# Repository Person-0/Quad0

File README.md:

# **Quad0**

*quadcopter with a custom flight controller, firmware that supports both brushed and brushless motors*

## **The Idea**
This is a custom flight controller with minimal stuff required to fly a quadcopter on-board, supporting both brushless and brushed motors.

Onboard components include:

- `RP2350A` Microcontroller Unit
- **IMU**:
    - `ICM-42688-P` Accelerometer & Gyroscope
    - `DPS368XTSA1` Barometer
    - `BMM150` Magnetometer

- MOSFET motor drivers (`DMN2024UFDF-7`) for brushed motors
- Pads to connect brushed / brushless motors
- Support for `ESP01 WiFi module` for brushed mode OR any radio receiver that supports SBUS or similar protocols for brushless mode

The board will be designed in a way such that it can fly with standard *8520 coreless motors* and a tiny lipo battery for brushed mode.

As for the brushless mode, I will be targeting `2204` size brushless motors with a `5inch` prop size, ~5inch frame configuration.

> For building, skip to [Build instructions](#build-instructions) section.

## **PCB**

The PCB 3D preview looks like this:

## **Schematics**

> *[Right Click >> Open in new tab] on the image to view properly.*

> Note that the PCB and schematic files can be opened using KiCAD. They are located in the `/PCB/Quad0` directory inside this repository.

Steps for viewing the PCB schematics and layout:
- Open KiCAD
- Click **File** (top left) >> **Open Project**
- Navigate to the the repository's saved destination,
- Open **/PCB/Quad0** directory
- Select the file `Quad0.kicad_pro`

## Brushed / Brushless Switch

- **Yellow**: Brushed motor connectors
- **Red**: Brushed / Brusheless Mode selection connector

**For Brushed:** Short both pads together using solder or by soldering 2.54mm headers and adding jumper.

**For Brushless:** Un-short both pads if shorted, connect ESC signal pin to the pad marked with the thick white circle.

Each Mode selection connector is placed closest to the motor output it controls.

## **CAD Frame**
> View [/CAD](./CAD/) directory for `.f3d` and `.step` files.

The frame for brushed version of the quadcopter was designed in Fusion360 and looks like this:

**The frame is divided into 3 separate parts:**

- **Main Frame:**

- **Duct Body:**

- **Cover:**

All the parts are made to friction-fit together using cylindrical extrusions and holes, the reason being to minimize the weight of the frame as using screws would add a LOT of weight. The friction fits would allow for either the cover or duct body to be omitted incase they are adding too much weight.

## **Firmware**

*Please checkout the [/Firmware](./Firmware/) directory to view the firmware source, current state and compiling / flashing instructions.*

> Note that the hardware is also [fully supported](https://betaflight.com/blog/2025/10/10/RP2350%20Lands%20in%20Betaflight) by [Betaflight](https://betaflight.com/). Instructions on how to setup betaflight will be provided after I physically test it myself to know what works.

## **Ordering Parts, PCBA**
1. **PCBA**

Files required (gerber, bom, cpl) for ordering PCB Assembly from JLCPCB are available in [PCB/Ordering/](./PCB/Ordering/) directory.

The grand total for this comes out to be at `$108.95`, including `$9.86` for shipping. This cost can be brought down using coupon codes and also using JLCPCB'S desktop app: JLCONE.

This is after minimizing extended components usage and using basic PCBA (cheapest option). The PCB quantity and PCBA quantity is the MOQ (minimum order quantity): 5, 2 respectively.

**Cart Screenshot:**

2. **Other components**

Components required other than the ones that the PCBA covers are the following (for brushed mode):
- 4x Coreless Motors
- 4x 65mm propellers (2CW + 2CCW)
- 1x 1N5819 Diode (6V version recommended)
- 1x 3.7v tiny LiPo battery (+ a charger for it if you do not have one). Recommended capacity ~350-500mAh, try to minimize weight
- 1x ESP-01 WiFi Module
- 2.54mm header pins as required (only if you need them, otherwise you can directly solder the wires to the pads)

### **BOM** (Region: India)
---
| S.No. | Item Name | Item Description | URL | Qty | Unit Price ($) | Effective Price ($) |
|---:|---|---|---|---:|---:|---:|
| 1 | JLCPCB Order | 5x PCB + 2x PCBA | - | 1 | 99.09 | 99.09 |
| 2 | JLCPCB Shipping | Shipping costs | - | 1 | 9.86 | 9.86 |
| 3 | 8520 Coreless Brushed Motor | 8520 Coreless motor | https://makerbazar.in/products/magnetic-micro-coreless-motor-for-drones-quadcopters-rc?variant=44950426812656 | 4 | 0.72 | 2.88 |
| 4 | 65mm 2 Blade Toothpick Propeller 1mm Shaft Pitch 1.3" Clear Red (4 Pair CW+CCW) | 65mm Propeller | https://evelta.com/gemfan-65mm-2-blade-toothpick-propeller-1mm-red/?sku=479-PMPC65S-R1&utm_matchtype=&utm_term=&adgroupid=&gc_id=21398421111&h_ad_id= | 1 | 2.20 | 2.20 |
| 5 | 1N5819 40V 1A Schottky Diode - Pack of 10 | Diode for reverse polarity protection | https://makerbazar.in/products/1n5819-schottky-diode-1a-40v-do-41?variant=48251131527408 | 1 | 0.20 | 0.20 |
| 6 | 3.7V 500mAH LiPo battery | 500 mAh LiPo battery | https://makerbazar.in/products/kp-drone-lipo-batteries-3-7v-rechargeable-battery-for-mini-rc-aircraft-quadcopters?variant=48251096662256 | 1 | 2.81 | 2.81 |
| 7 | ESP-01 ESP8266 Serial WIFI Transceiver Module | ESP01 WiFi module | https://makerbazar.in/products/esp8266-wifi-module-for-arduino?variant=31789289898080 | 1 | 1.41 | 1.41 |
| | | | | | **Total:** | **127.50** |

This does not include shipping costs for components other than PCB+PCBA, since that will differ from place-to-place.

## **Build Instructions**

The project build is divided into 4 parts:
1. PCB, Components ordering
2. Soldering external components onto the PCB
3. 3D printing the frame
4. Compiling, Flashing the firmware.

### 1.) PCB, Components Ordering
Please refer the [Ordering Parts, PCBA](#ordering-parts-pcba) section for this step.

### 2.) Soldering external components onto the PCB
Various components are required to be externally hand soldered onto the PCB. Focusing on the brushed mode, these are the components:
1. **Brushed Motors**: These need to be soldered to the motor pads at the corner ends of the PCB. Make sure that the Mode selection connector pads that are present near the motor connectors are shorted for brushed mode. This might require re-soldering to change motor polarity so keep that in mind.
2. **1N5819 Diode**: This needs to be soldered on the 2.54mm header pad with silkscreen marked as "1N5819". The cathode should be connected to the pad with the silkscreen square connected to the silkscreen text (This is the +BATT_Brushed pad).
3. **Battery Connector**: Marked as "Power IN" on the silkscreen with + and - symbols, either use JST style male-female connectors (preferred) or simple jumper wires. Solder the female connector to the PCB and the male one to the battery terminals. Ensure you can charge the battery easily and handle the LiPo batteries properly as they are extremely dangerous. Battery can be fixed using rubber bands or double-sided tape onto the backside of the frame. Make sure to center it as accurately as close to the Quad's centre-of-gravity, so as to ensure stable flight
4. **ESP-01**: Solder the ESP-01 module to the top footprint defined for it. You can refer the 3D frame render for orientation as it shows the correct way it needs to be placed. Your module most likely will already have headers soldered onto it, you just need to solder it onto the PCB.
5. **GPIO Pins (optional)**: At the bottom of the PCB, if needed, solder female header pins or just solder the extra components directly.

### 3.) 3D printing the frame + assembling
The following three `.step` files need to be 3d printed separately using a lightweight but sturdy material of your choice: (I will be testing it out myself, starting with PLA)
- [MainBody.step](./CAD/exports/MainBody.step)
- [DuctBody.step](./CAD/exports/DuctBody.step)
- [Cover.step](./CAD/exports/Cover.step)

After that, It is recommended to test the quad with just the MainBody and then progressively add the DuctBody, Cover. This helps to ensure that the drone actually flies and is not held down by the weight of the frame.

The PCB sits on the cylindrical extrusions defined for it (as shown in the preview images). You can add tiny foam/similar rings between the PCB and the plastic body to dampen motor vibrations. Use adhesive tape (or whatever you prefer) to firmly hold the PCB in place with the main body, while also making sure you do not add extra unnecessary weight.

### 4.) Compiling, Flashing the firmware
Please refer the [/Firmware](./Firmware/) directory for this step.

That's it!

## 😼💖

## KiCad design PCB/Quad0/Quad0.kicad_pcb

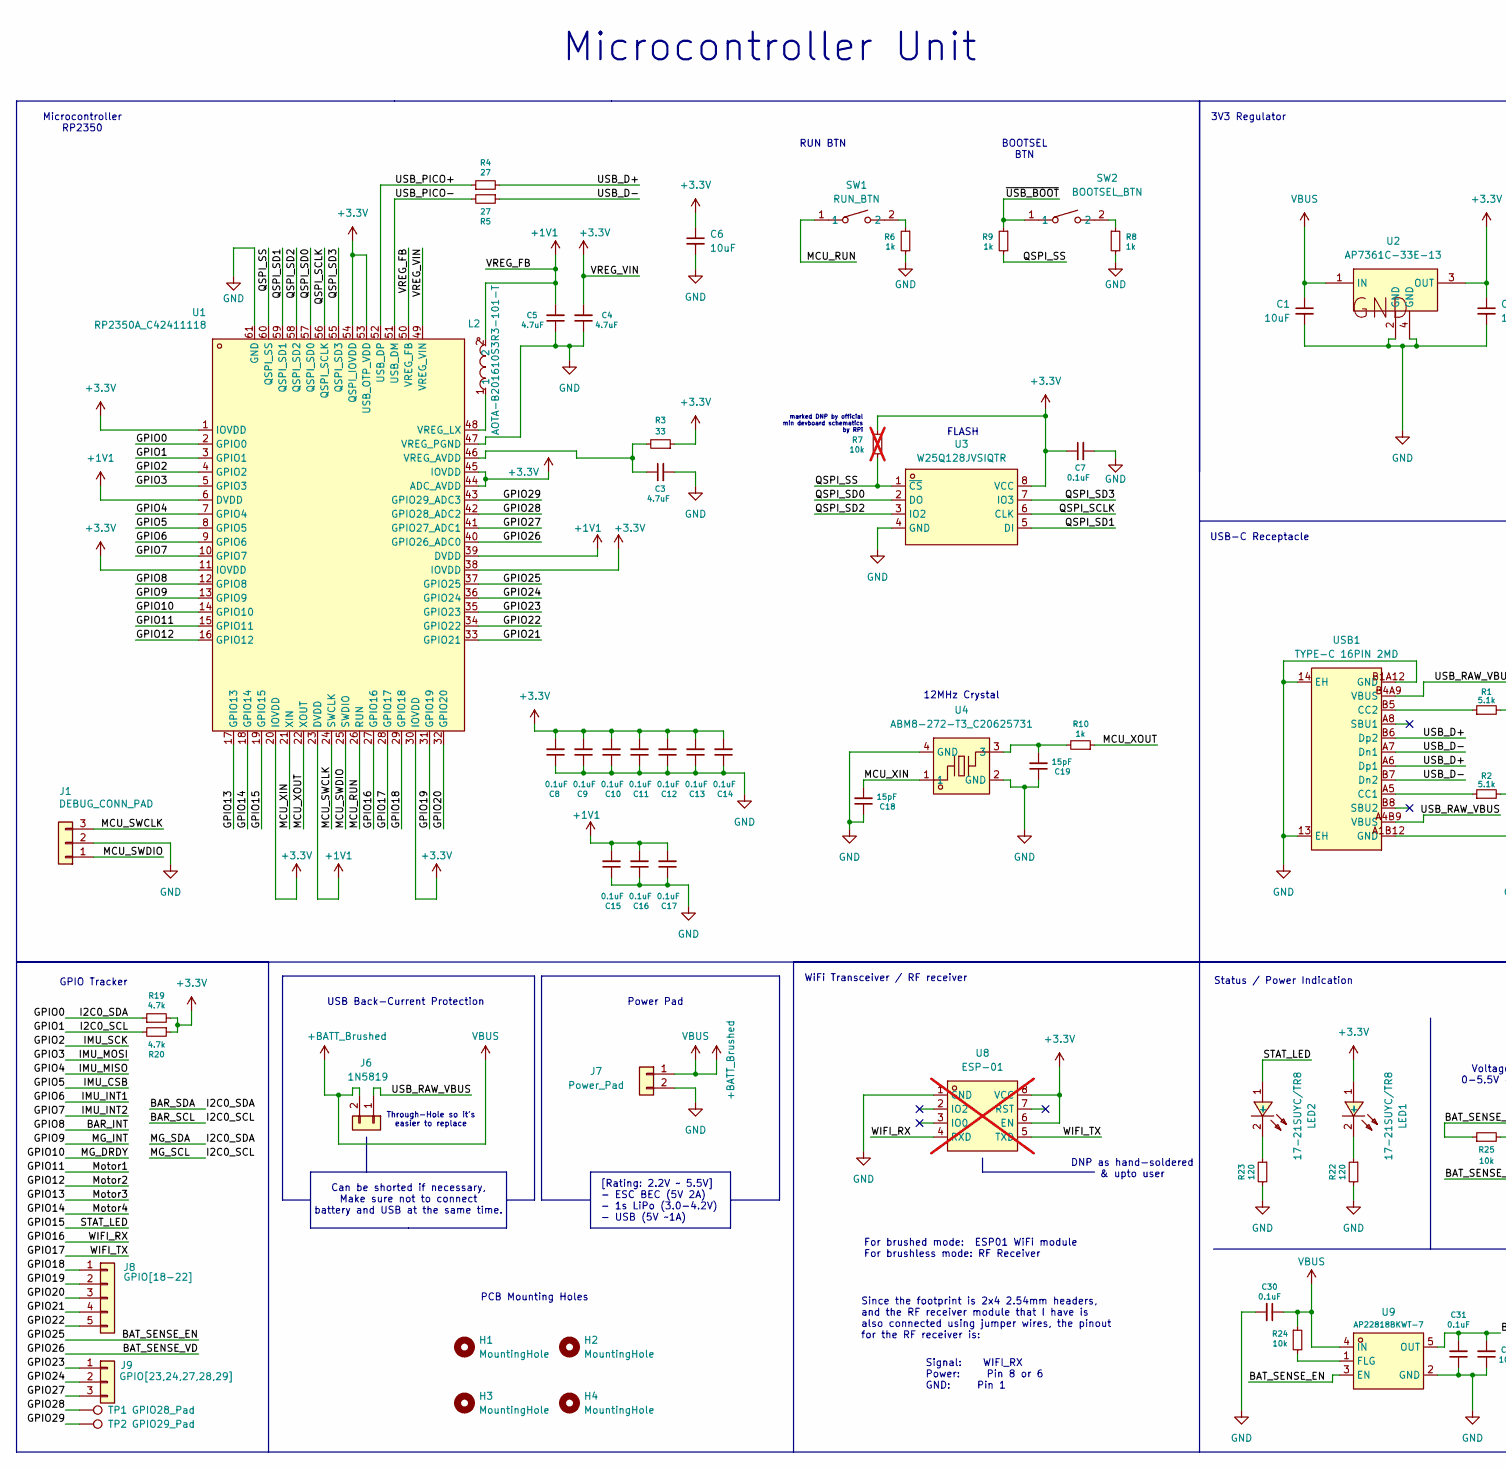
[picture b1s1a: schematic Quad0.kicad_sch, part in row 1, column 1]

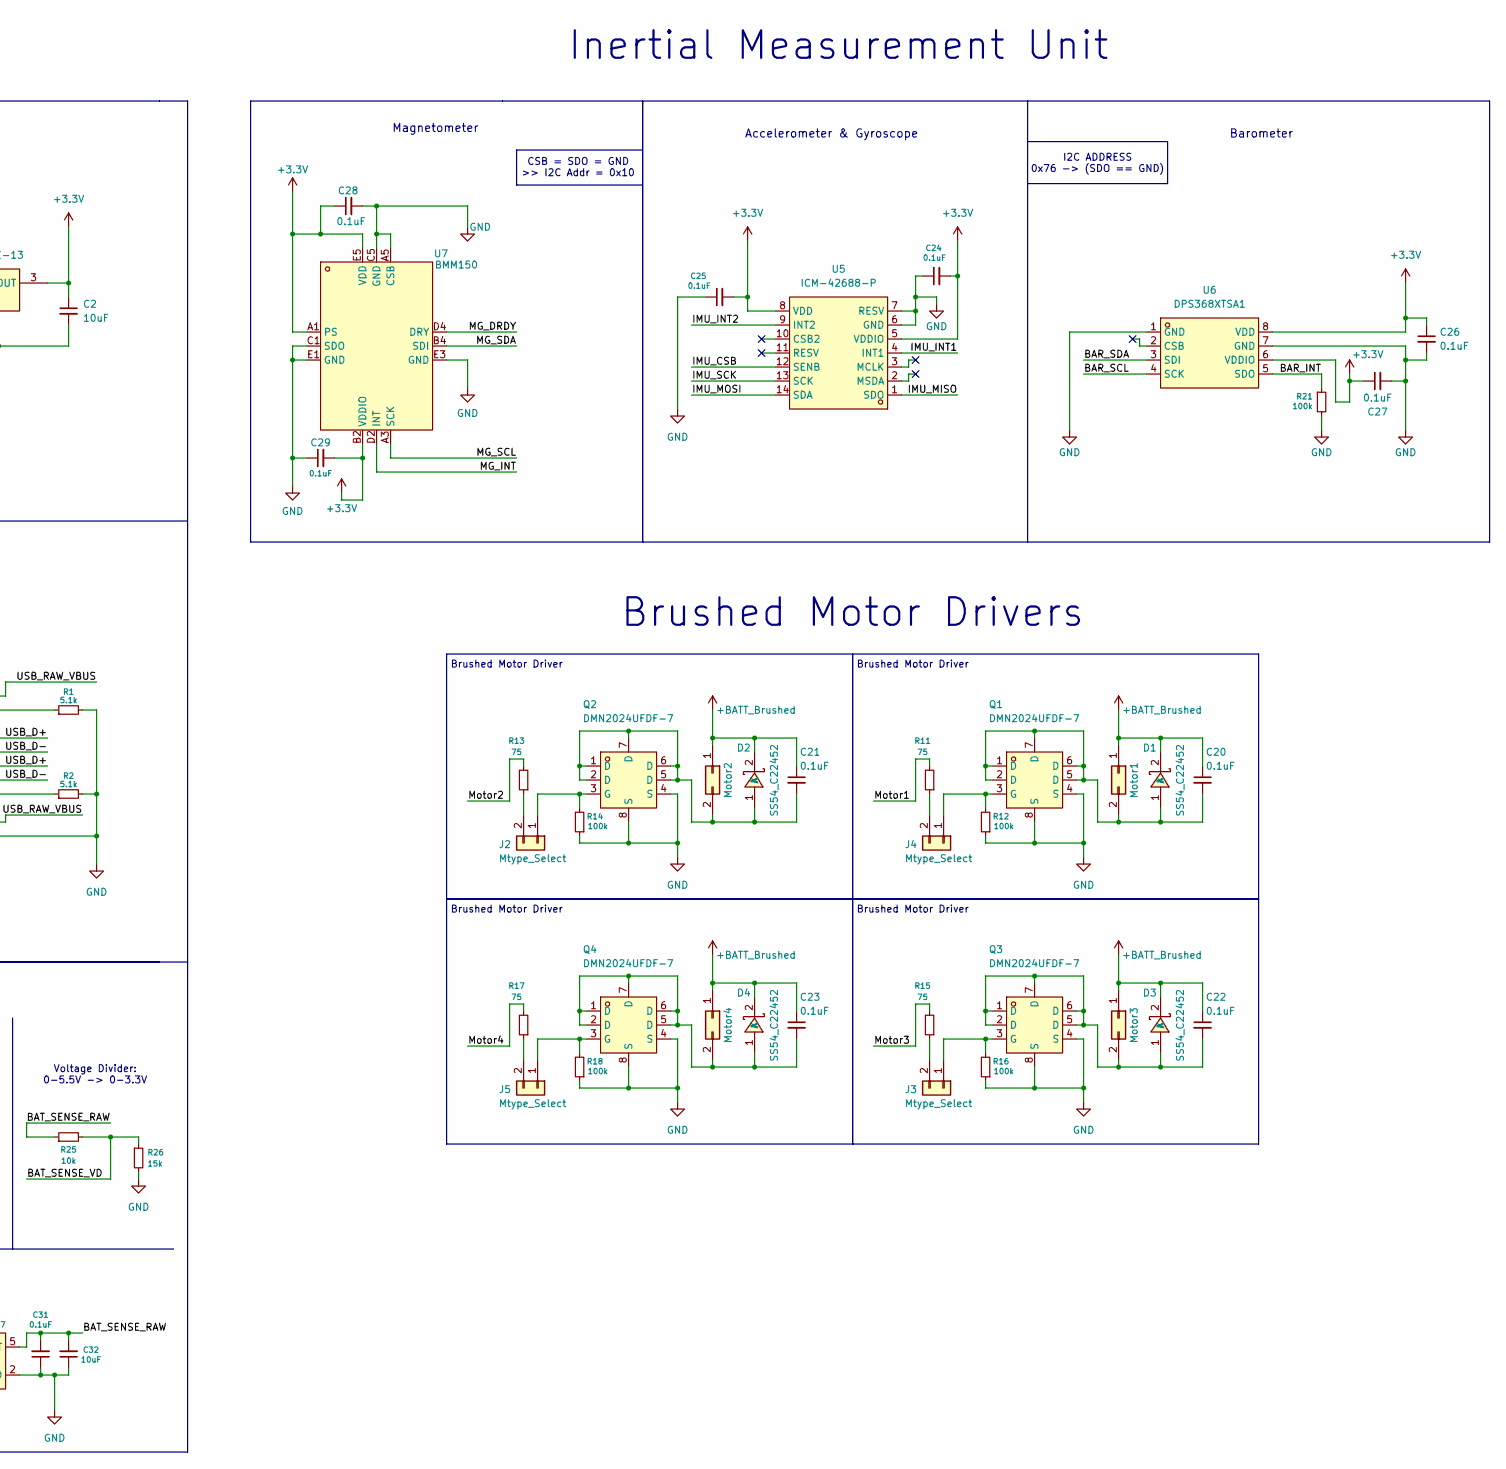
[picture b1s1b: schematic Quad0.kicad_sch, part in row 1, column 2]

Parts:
C1, C2, C6, C32: 10uF; C0603; MPN CL10A106KP8NNNC; LCSC Part C19702
C3, C4, C5: 4.7uF; C0402; MPN GRM155R61A475KEAAD; LCSC Part C77004
C7, C8, C9, C10, C11, C12, C13, C14, C15, C16, C17, C20, C21, C22, C23, C24, C25, C26, C27, C28, C29, C30, C31: 0.1uF; C0402; MPN CL05B104KO5NNNC; LCSC Part C1525
C18, C19: 15pF; C0402; MPN CC0402JRNPO9BN150; LCSC Part C106997
D1, D2, D3, D4: SS54_C22452; SMA_L4.4-W2.8-LS5.4-R-RD; MPN SS54; LCSC Part C22452
H1, H2, H3, H4: MountingHole; MountingHole_2mm
J1: DEBUG_CONN_PAD; PinHeader_1x03_P2.54mm_Vertical
J2, J3, J4, J5: Mtype_Select; PinHeader_1x02_P2.54mm_Vertical
J6: 1N5819; PinHeader_1x02_P2.54mm_Vertical
J7: Power_Pad; PinHeader_1x02_P2.54mm_Vertical
J8: GPIO[18-22]; PinHeader_1x05_P2.54mm_Vertical
J9: GPIO[23,24,27,28,29]; PinHeader_1x03_P2.54mm_Vertical
L2: AOTA-B201610S3R3-101-T; IND-SMD_L2.0-W1.6_AOTA-B201610S3R3-101-T; MPN AOTA-B201610S3R3-101-T; LCSC Part C42411119
LED1, LED2: 17-21SUYC/TR8; LED0805-R-RD; MPN KT-0805黄灯; LCSC Part C2296
Motor1, Motor2, Motor3, Motor4: motor; PinHeader_1x02_P2.54mm_Vertical
Q1, Q2, Q3, Q4: DMN2024UFDF-7; DFN2020MD-6_L2.0-W2.0-P0.65-BL; MPN DMN2024UFDF-7; LCSC Part C5248840
R1, R2: 5.1k; R0402; MPN 0402WGF5101TCE; LCSC Part C25905
R3: 33; R0402; MPN 0402WGF330JTCE; LCSC Part C25105
R4, R5: 27; R0402; MPN 0402WGF270JTCE; LCSC Part C25100
R6, R8, R9, R10: 1k; R0402; MPN 0402WGF1001TCE; LCSC Part C11702
R7: 10k; not fitted
R11, R13, R15, R17: 75; R0603; MPN 0603WAF750JT5E; LCSC Part C4275
R12, R14, R16, R18, R21: 100k; R0402; MPN 0402WGF1003TCE; LCSC Part C25741
R19, R20: 4.7k; R0402; MPN 0402WGF4701TCE; LCSC Part C25900
R22, R23: 120; R0402; MPN 0402WGF1200TCE; LCSC Part C25079
R24, R25: 10k; R0402; MPN 0402WGF1002TCE; LCSC Part C25744
R26: 15k; R0402; MPN 0402WGF1502TCE; LCSC Part C25756
SW1: RUN_BTN; SW-SMD_L3.9-W3.0-P4.45; MPN TS-1088-AR02016; LCSC Part C720477
SW2: BOOTSEL_BTN; SW-SMD_L3.9-W3.0-P4.45; MPN TS-1088-AR02016; LCSC Part C720477
TP1: GPIO28_Pad; TestPoint_Pad_D1.0mm
TP2: GPIO29_Pad; TestPoint_Pad_D1.0mm
U1: RP2350A_C42411118; QFN-60_L7.0-W7.0-P0.40-TL-EP3.4; MPN RP2350A; LCSC Part C42411118
U2: AP7361C-33E-13; SOT-223_L6.5-W3.5-P2.30-LS7.0-BR; MPN AP7361C-33E-13; LCSC Part C500795
U3: W25Q128JVSIQTR; SOIC-8_L5.3-W5.3-P1.27-LS8.0-BL; MPN W25Q128JVSIQ; LCSC Part C97521
U4: ABM8-272-T3_C20625731; CRYSTAL-SMD_4P-L3.2-W2.5-BL; MPN ABM8-272-T3; LCSC Part C20625731
U5: ICM-42688-P; LGA-14_L3.0-W2.5-P0.50-BL; MPN ICM-42688-P(TOKMAS); LCSC Part C54308212
U6: DPS368XTSA1; LGA-8_L2.5-W2.0-P0.65-TR_DPS368; MPN DPS368XTSA1(TOKMAS); LCSC Part C55090144
U7: BMM150; WLCSP-12_L1.6-W1.6_BMM150; MPN BMM150; LCSC Part C171681
U8: ESP-01; WIFIM-TH_8P-L24.7-W14.4-P2.54; MPN ESP-01; LCSC Part C503581; not fitted
U9: AP22818BKWT-7; TSOT-23-5_L2.9-W1.6-P0.95-LS2.8-BL; MPN AP22818BKWT-7; LCSC Part C5564097
USB1: TYPE-C 16PIN 2MD; USB-C-SMD_TYPE-C-16PIN-2MD-073; MPN TYPE-C 16PIN 2MD(073); LCSC Part C2765186

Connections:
+1V1: C5.2, C15.2, C16.2, C17.2, L2.2, U1.6 (DVDD), U1.23 (DVDD), U1.39 (DVDD), U1.50 (VREG_FB)
+3.3V: C2.1, C4.2, C6.1, C7.1, C8.2, C9.2, C10.2, C11.2, C12.2, C13.2, C14.2, C24.2, C25.2, C26.1, C27.1, C28.1, C29.2, LED1.1 (+), R3.1, R7.1, R19.2, R20.1, U1.1 (IOVDD), U1.11 (IOVDD), U1.20 (IOVDD), U1.30 (IOVDD), U1.38 (IOVDD), U1.44 (ADC_AVDD), U1.45 (IOVDD), U1.49 (VREG_VIN), U1.53 (USB_OTP_VDD), U1.54 (QSPI_IOVDD), U2.3 (OUT), U3.8 (VCC), U5.5 (VDDIO), U5.8 (VDD), U6.6 (VDDIO), U6.8 (VDD), U7.A1 (PS), U7.B2 (VDDIO), U7.E5 (VDD), U8.6 (EN), U8.8 (VCC)
+BATT_Brushed: C1.1, C20.1, C21.1, C22.1, C23.1, C30.1, D1.2 (K), D2.2 (K), D3.2 (K), D4.2 (K), J6.2, J7.1, Motor1.1, Motor2.1, Motor3.1, Motor4.1, R24.1, U2.1 (IN), U9.4 (IN)
/BAR_INT: R21.1, U1.12 (GPIO8), U6.5 (SDO)
/BAR_SCL: R20.2, U1.3 (GPIO1), U6.4 (SCK), U7.A3 (SCK)
/BAR_SDA: R19.1, U1.2 (GPIO0), U6.3 (SDI), U7.B4 (SDI)
/BAT_SENSE_EN: U1.37 (GPIO25), U9.3 (EN)
/BAT_SENSE_RAW: C31.2, C32.2, R25.1, U9.5 (OUT)
/BAT_SENSE_VD: R25.2, R26.1, U1.40 (GPIO26_ADC0)
/GPIO2: U1.4 (GPIO2), U5.13 (SCK)
/GPIO3: U1.5 (GPIO3), U5.14 (SDA)
/GPIO4: U1.7 (GPIO4), U5.1 (SDO)
/GPIO5: U1.8 (GPIO5), U5.12 (SENB)
/GPIO6: U1.9 (GPIO6), U5.4 (INT1)
/GPIO7: U1.10 (GPIO7), U5.9 (INT2)
/GPIO9: U1.13 (GPIO9), U7.D2 (INT)
/GPIO10: U1.14 (GPIO10), U7.D4 (DRY)
/GPIO11: R11.2, U1.15 (GPIO11)
/GPIO12: R13.2, U1.16 (GPIO12)
/GPIO13: R15.2, U1.17 (GPIO13)
/GPIO14: R17.2, U1.18 (GPIO14)
/GPIO15: LED2.1 (+), U1.19 (GPIO15)
/GPIO16: U1.27 (GPIO16), U8.4 (RXD)
/GPIO17: U1.28 (GPIO17), U8.5 (TXD)
/GPIO18: J8.1, U1.29 (GPIO18)
/GPIO19: J8.2, U1.31 (GPIO19)
/GPIO20: J8.3, U1.32 (GPIO20)
/GPIO21: J8.4, U1.33 (GPIO21)
/GPIO22: J8.5, U1.34 (GPIO22)
/GPIO23: J9.1, U1.35 (GPIO23)
/GPIO24: J9.2, U1.36 (GPIO24)
/GPIO27: J9.3, U1.41 (GPIO27_ADC1)
/GPIO28: TP1.1, U1.42 (GPIO28_ADC2)
/GPIO29: TP2.1, U1.43 (GPIO29_ADC3)
/MCU_RUN: SW1.1, U1.26 (RUN)
/MCU_SWCLK: J1.3, U1.24 (SWCLK)
/MCU_SWDIO: J1.1, U1.25 (SWDIO)
/MCU_XIN: C18.2, U1.21 (XIN), U4.1
/MCU_XOUT: R10.1, U1.22 (XOUT)
/QSPI_SCLK: U1.56 (QSPI_SCLK), U3.6 (CLK)
/QSPI_SD0: U1.57 (QSPI_SD0), U3.2 (DO)
/QSPI_SD1: U1.59 (QSPI_SD1), U3.5 (DI)
/QSPI_SD2: U1.58 (QSPI_SD2), U3.3 (IO2)
/QSPI_SD3: U1.55 (QSPI_SD3), U3.7 (IO3)
/QSPI_SS: R7.2, R9.2, U1.60 (QSPI_SS), U3.1 (~CS)
/USB_D+: R4.2, USB1.A6 (Dp1), USB1.B6 (Dp2)
/USB_D-: R5.1, USB1.A7 (Dn1), USB1.B7 (Dn2)
/USB_PICO+: R4.1, U1.52 (USB_DP)
/USB_PICO-: R5.2, U1.51 (USB_DM)
/USB_RAW_VBUS: J6.1, USB1.A4B9 (VBUS), USB1.B4A9 (VBUS)
/~USB_BOOT: R9.1, SW2.1
GND: C1.2, C2.2, C3.2, C4.1, C5.1, C6.2, C7.2, C8.1, C9.1, C10.1, C11.1, C12.1, C13.1, C14.1, C15.1, C16.1, C17.1, C18.1, C19.1, C24.1, C25.1, C26.2, C27.2, C28.2, C29.1, C30.2, C31.1, C32.1, J1.2, J7.2, Q1.4 (S), Q1.8 (S), Q2.4 (S), Q2.8 (S), Q3.4 (S), Q3.8 (S), Q4.4 (S), Q4.8 (S), R1.2, R2.2, R6.2, R8.2, R12.1, R14.1, R16.1, R18.1, R21.2, R22.2, R23.2, R26.2, U1.47 (VREG_PGND), U1.61 (GND), U2.2 (GND), U2.4 (GND), U3.4 (GND), U4.2 (GND), U4.4 (GND), U5.6 (GND), U5.7 (RESV), U6.1 (GND), U6.7 (GND), U7.A5 (CSB), U7.C1 (SDO), U7.C5 (GND), U7.E1 (GND), U7.E3 (GND), U8.1 (GND), U9.2 (GND), USB1.13 (EH), USB1.14 (EH), USB1.A1B12 (GND), USB1.B1A12 (GND)
unnamed: C19.2, R10.2, U4.3
unnamed: C20.2, D1.1 (A), Motor1.2, Q1.1 (D), Q1.2 (D), Q1.5 (D), Q1.6 (D), Q1.7 (D)
unnamed: C21.2, D2.1 (A), Motor2.2, Q2.1 (D), Q2.2 (D), Q2.5 (D), Q2.6 (D), Q2.7 (D)
unnamed: C22.2, D3.1 (A), Motor3.2, Q3.1 (D), Q3.2 (D), Q3.5 (D), Q3.6 (D), Q3.7 (D)
unnamed: C23.2, D4.1 (A), Motor4.2, Q4.1 (D), Q4.2 (D), Q4.5 (D), Q4.6 (D), Q4.7 (D)
unnamed: J2.1, Q2.3 (G), R14.2
unnamed: J2.2, R13.1
unnamed: J3.2, R15.1
unnamed: J3.1, Q3.3 (G), R16.2
unnamed: J4.1, Q1.3 (G), R12.2
unnamed: J4.2, R11.1
unnamed: J5.1, Q4.3 (G), R18.2
unnamed: J5.2, R17.1
unnamed: LED1.2 (-), R22.1
unnamed: LED2.2 (-), R23.1
unnamed: R6.1, SW1.2
unnamed: R8.1, SW2.2
unnamed: C3.1, R3.2, U1.46 (VREG_AVDD)
unnamed: L2.1, U1.48 (VREG_LX)
unnamed: R24.2, U9.1 (FLG)
unnamed: R2.1, USB1.A5 (CC1)
unnamed: R1.1, USB1.B5 (CC2)

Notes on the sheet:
12MHz Crystal
Microcontroller Unit
Through-Hole so it's easier to replace
Brushed Motor Driver
WiFi Transceiver / RF receiver
Can be shorted if necessary, Make sure not to connect battery and USB at the same time.
Brushed Motor Drivers
marked DNP by official min devboard schematics by RPi
Voltage Divider: 0-5.5V -> 0-3.3V
DNP as hand-soldered & upto user
I2C ADDRESS 0x76 -> (SDO == GND)
RUN BTN
[Rating: 2.2V ~ 5.5V] - ESC BEC (5V 2A) - 1s LiPo (3.0-4.2V) - USB (5V ~1A)
Status / Power Indication
Barometer
Signal: WIFI_RX Power: Pin 8 or 6 GND: Pin 1
Since the footprint is 2x4 2.54mm headers, and the RF receiver module that I have is also connected using jumper wires, the pinout for the RF receiver is:
CSB = SDO = GND >> I2C Addr = 0x10
USB-C Receptacle
GPIO Tracker
3V3 Regulator
BOOTSEL BTN
Inertial Measurement Unit
USB Back-Current Protection
Accelerometer & Gyroscope
FLASH
Microcontroller RP2350
PCB Mounting Holes
Magnetometer
Power Pad
For brushed mode: ESP01 WiFi module For brushless mode: RF Receiver

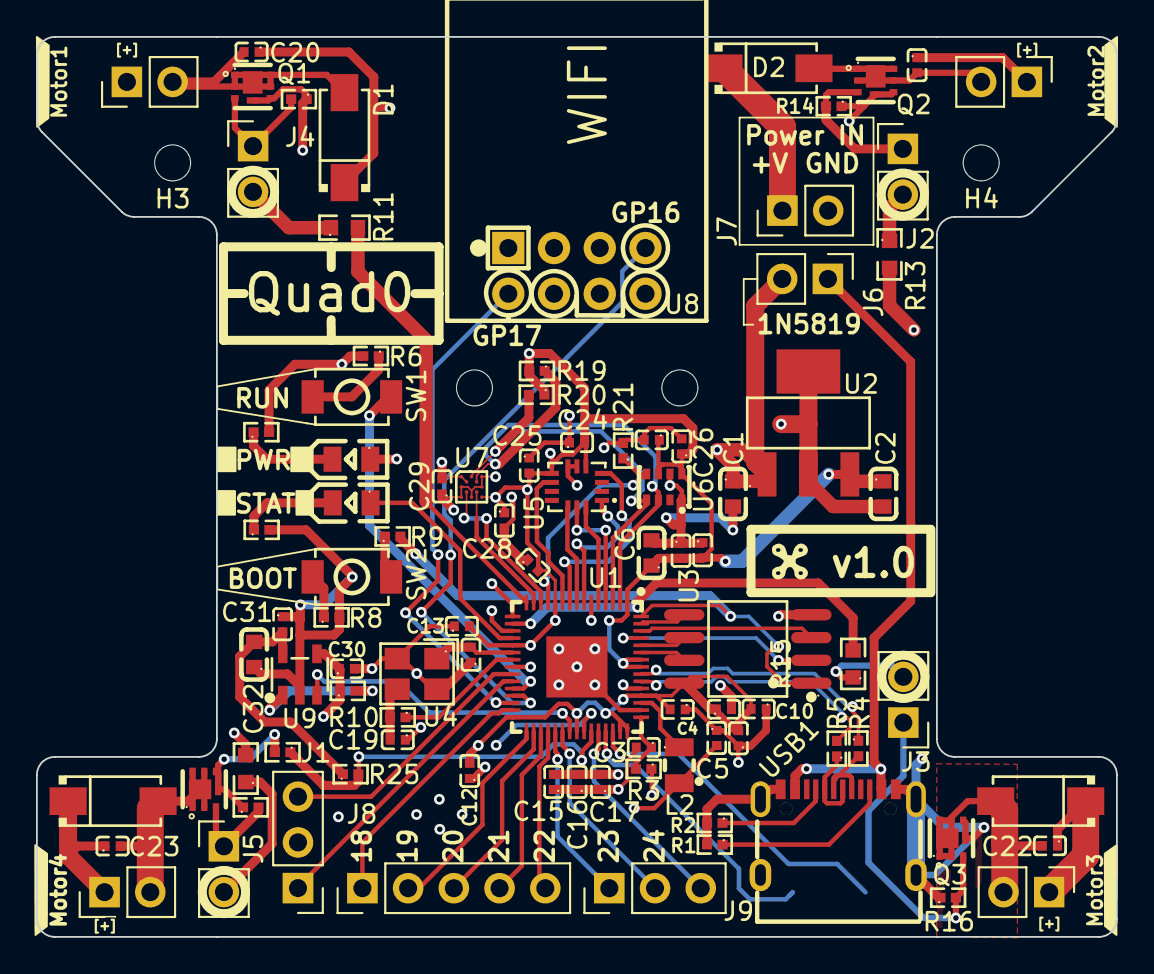
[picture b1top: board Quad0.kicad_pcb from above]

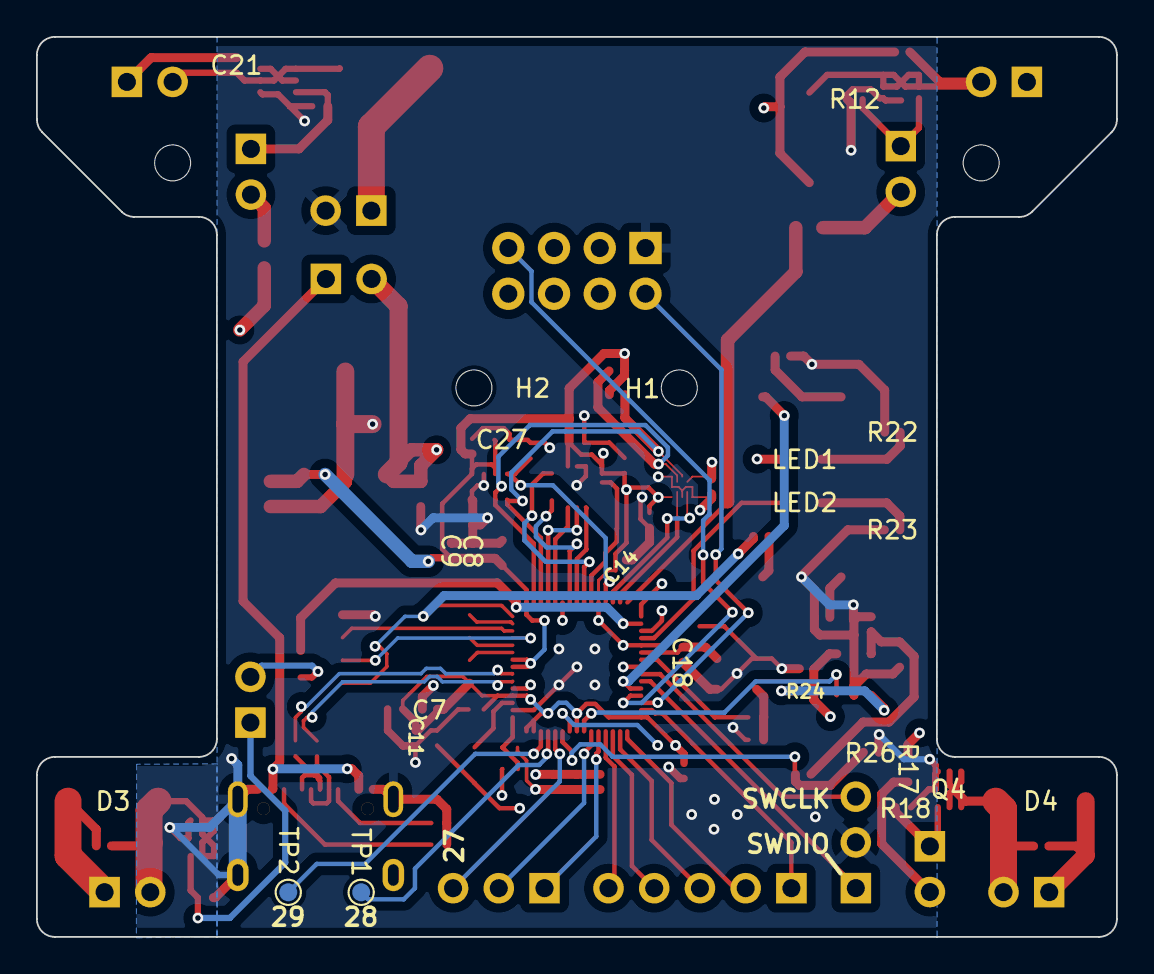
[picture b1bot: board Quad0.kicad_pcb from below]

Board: 4 copper layers, 60.0 x 50.0 mm, 99 parts (2 on the bottom side), 74 nets.

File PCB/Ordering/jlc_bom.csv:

"Designator","Qty","Value","DNP","Exclude from BOM","Exclude from Board","Footprint","Datasheet","MPN","Manufacturer","LCSC Part","Description"
"C1,C2,C6,C32","4","10uF","","","","easyeda2kicad:C0603","https://jlc-prod-smt.oss-eu-central-1.aliyuncs.com/smtDataMa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","CL10A106KP8NNNC","Samsung Electro-Mechanics","C19702","Unpolarized capacitor, small symbol"
"C3,C4,C5","3","4.7uF","","","","easyeda2kicad:C0402","https://jlc-prod-smt.oss-eu-central-1.aliyuncs.com/smtDataMa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","GRM155R61A475KEAAD","Murata Electronics","C77004","Unpolarized capacitor, small symbol"
"C7,C8,C9,C10,C11,C12,C13,C14,C15,C16,C17,C20,C21,C22,C23,C24,C25,C26,C27,C28,C29,C30,C31","23","0.1uF","","","","easyeda2kicad:C0402","https://jlc-prod-smt.oss-eu-central-1.aliyuncs.com/smtDataMa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","CL05B104KO5NNNC","Samsung Electro-Mechanics","C1525","Unpolarized capacitor, small symbol"
"C18,C19","2","15pF","","","","easyeda2kicad:C0402","https://jlc-prod-smt.oss-eu-central-1.aliyuncs.com/smtDataMa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","CC0402JRNPO9BN150","YAGEO","C106997","Unpolarized capacitor, small symbol"
"D1,D2,D3,D4","4","SS54_C22452","","","","easyeda2kicad:SMA_L4.4-W2.8-LS5.4-R-RD","https://lcsc.com/product-detail/Schottky-Barrier-Diodes-SBD_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","SS54","MDD(辰达半导体)","C22452","SS54"
"H1,H2,H3,H4,J1,J2,J3,J4,J5,J6,J7,J8,J9,Motor1,Motor2,Motor3,Motor4,R7,TP1,TP2","20","10k,1N5819,DEBUG_CONN_PAD,GPIO28_Pad,GPIO29_Pad,GPIO[18-22],GPIO[23,24,27,28,29],MountingHole,Mtype_Select,Power_Pad,motor","DNP","Excluded from BOM","","Connector_PinHeader_2.54mm:PinHeader_1x02_P2.54mm_Vertical,Connector_PinHeader_2.54mm:PinHeader_1x03_P2.54mm_Vertical,Connector_PinHeader_2.54mm:PinHeader_1x05_P2.54mm_Vertical,MountingHole:MountingHole_2mm,TestPoint:TestPoint_Pad_D1.0mm","~","","","","Generic connector, double row, 02x01, this symbol is compatible with counter-clockwise, top-bottom and odd-even numbering schemes., script generated (kicad-library-utils/schlib/autogen/connector/),Generic connector, single row, 01x02, script generated (kicad-library-utils/schlib/autogen/connector/),Generic connector, single row, 01x03, script generated (kicad-library-utils/schlib/autogen/connector/),Generic connector, single row, 01x05, script generated (kicad-library-utils/schlib/autogen/connector/),Mounting Hole without connection,Resistor, small symbol,test point"
"L2","1","AOTA-B201610S3R3-101-T","","","","easyeda2kicad:IND-SMD_L2.0-W1.6_AOTA-B201610S3R3-101-T","https://www.lcsc.com/datasheet/C42411119.pdf","AOTA-B201610S3R3-101-T","ABRACON","C42411119",""
"LED1,LED2","2","17-21SUYC/TR8","","","","easyeda2kicad:LED0805-R-RD","https://lcsc.com/product-detail/Light-Emitting-Diodes-LED_Ye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","KT-0805黄灯","KENTO","C2296","0805"
"Q1,Q2,Q3,Q4","4","DMN2024UFDF-7","","","","easyeda2kicad:DFN2020MD-6_L2.0-W2.0-P0.65-BL","https://www.lcsc.com/datasheet/C5248840.pdf","DMN2024UFDF-7","DIODES(美台)","C5248840",""
"R1,R2","2","5.1k","","","","easyeda2kicad:R0402","https://jlc-prod-smt.oss-eu-central-1.aliyuncs.com/smtDataMa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","0402WGF5101TCE","UNI-ROYAL(Uniroyal Elec)","C25905","Resistor, small symbol"
"R3","1","33","","","","easyeda2kicad:R0402","https://jlc-prod-smt.oss-eu-central-1.aliyuncs.com/smtDataMa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","0402WGF330JTCE","UNI-ROYAL(Uniroyal Elec)","C25105","Resistor, small symbol"
"R4,R5","2","27","","","","easyeda2kicad:R0402","https://jlc-prod-smt.oss-eu-central-1.aliyuncs.com/smtDataMa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","0402WGF270JTCE","UNI-ROYAL(Uniroyal Elec)","C25100","Resistor, small symbol"
"R6,R8,R9,R10","4","1k","","","","easyeda2kicad:R0402","https://jlc-prod-smt.oss-eu-central-1.aliyuncs.com/smtDataMa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","0402WGF1001TCE","UNI-ROYAL(Uniroyal Elec)","C11702","Resistor, small symbol"
"R11,R13,R15,R17","4","75","","","","easyeda2kicad:R0603","https://jlc-prod-smt.oss-eu-central-1.aliyuncs.com/smtDataMa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","0603WAF750JT5E","UNI-ROYAL(Uniroyal Elec)","C4275","Resistor, small symbol"
"R12,R14,R16,R18,R21","5","100k","","","","easyeda2kicad:R0402","https://jlc-prod-smt.oss-eu-central-1.aliyuncs.com/smtDataMa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","0402WGF1003TCE","UNI-ROYAL(Uniroyal Elec)","C25741","Resistor, small symbol"
"R19,R20","2","4.7k","","","","easyeda2kicad:R0402","https://jlc-prod-smt.oss-eu-central-1.aliyuncs.com/smtDataMa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","0402WGF4701TCE","UNI-ROYAL(Uniroyal Elec)","C25900","Resistor, small symbol"
"R22,R23","2","120","","","","easyeda2kicad:R0402","https://jlc-prod-smt.oss-eu-central-1.aliyuncs.com/smtDataMa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","0402WGF1200TCE","UNI-ROYAL(Uniroyal Elec)","C25079","Resistor, small symbol"
"R24,R25","2","10k","","","","easyeda2kicad:R0402","https://jlc-prod-smt.oss-eu-central-1.aliyuncs.com/smtDataMa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","0402WGF1002TCE","UNI-ROYAL(Uniroyal Elec)","C25744","Resistor, small symbol"
"R26","1","15k","","","","easyeda2kicad:R0402","https://jlc-prod-smt.oss-eu-central-1.aliyuncs.com/smtDataMa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","0402WGF1502TCE","UNI-ROYAL(Uniroyal Elec)","C25756","Resistor, small symbol"
"SW1,SW2","2","BOOTSEL_BTN,RUN_BTN","","","","easyeda2kicad:SW-SMD_L3.9-W3.0-P4.45","https://lcsc.com/product-detail/Tactile-Switches_XUNPU-TS-10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","TS-1088-AR02016","XUNPU(讯普)","C720477",""
"U1","1","RP2350A_C42411118","","","","easyeda2kicad:QFN-60_L7.0-W7.0-P0.40-TL-EP3.4","https://www.lcsc.com/datasheet/C42411118.pdf","RP2350A","Raspberry Pi(树莓派)","C42411118",""
"U2","1","AP7361C-33E-13","","","","easyeda2kicad:SOT-223_L6.5-W3.5-P2.30-LS7.0-BR","https://lcsc.com/product-detail/New-Arrivals_Diodes-Incorpor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","AP7361C-33E-13","DIODES(美台)","C500795",""
"U3","1","W25Q128JVSIQTR","","","","easyeda2kicad:SOIC-8_L5.3-W5.3-P1.27-LS8.0-BL","https://lcsc.com/product-detail/FLASH_W25Q128JVSIQTR_C97521.html","W25Q128JVSIQ","Winbond(华邦)","C97521",""
"U4","1","ABM8-272-T3_C20625731","","","","easyeda2kicad:CRYSTAL-SMD_4P-L3.2-W2.5-BL","https://www.lcsc.com/datasheet/C20625731.pdf","ABM8-272-T3","ABRACON","C20625731",""
"U5","1","ICM-42688-P","","","","easyeda2kicad:LGA-14_L3.0-W2.5-P0.50-BL","https://www.lcsc.com/datasheet/C54308212.pdf","ICM-42688-P(TOKMAS)","Tokmas(托克马斯)","C54308212",""
"U6","1","DPS368XTSA1","","","","easyeda2kicad:LGA-8_L2.5-W2.0-P0.65-TR_DPS368","https://www.lcsc.com/datasheet/C55090144.pdf","DPS368XTSA1(TOKMAS)","Tokmas(托克马斯)","C55090144",""
"U7","1","BMM150","","","","easyeda2kicad:WLCSP-12_L1.6-W1.6_BMM150","https://lcsc.com/product-detail/Sensors_Bosch_BMM150_BMM150_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","BMM150","Bosch(博世)","C171681",""
"U8","1","ESP-01","DNP","Excluded from BOM","","easyeda2kicad:WIFIM-TH_8P-L24.7-W14.4-P2.54","https://lcsc.com/product-detail/WIFI-Modules_Ai-Thinker-ESP-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","ESP-01","Ai-Thinker(安信可)","C503581",""
"U9","1","AP22818BKWT-7","","","","easyeda2kicad:TSOT-23-5_L2.9-W1.6-P0.95-LS2.8-BL","https://www.lcsc.com/datasheet/C5564097.pdf","AP22818BKWT-7","DIODES(美台)","C5564097",""
"USB1","1","TYPE-C 16PIN 2MD","","","","easyeda2kicad:USB-C-SMD_TYPE-C-16PIN-2MD-073","https://www.lcsc.com/datasheet/C2765186.pdf","TYPE-C 16PIN 2MD(073)","SHOU HAN(首韩)","C2765186",""

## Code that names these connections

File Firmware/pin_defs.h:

// Wifi / Receiver
#define WIFI_UART_BLOCK  1
#define WIFI_RX         16
#define WIFI_TX         17

// Barometer
#define BAR_SDA          0
#define BAR_SCL          1
#define BAR_INT          8

// Magnetometer
#define MG_SDA           0
#define MG_SCL           1
#define MG_INT           9
#define MG_DRDY         10

// Accelerometer / Gyroscope
#define IMU_SCL          2
#define IMU_MOSI         3
#define IMU_MISO         4
#define IMU_CSB          5
#define IMU_INT1         6
#define IMU_INT2         7

// Motor drivers / ESC connection
#define MOTOR1          11
#define MOTOR2          12
#define MOTOR3          13
#define MOTOR4          14

// Battery info
#define BAT_SENSE_EN    25
#define BAT_SENSE_VD    26

// MISC
#define STAT_LED        15
